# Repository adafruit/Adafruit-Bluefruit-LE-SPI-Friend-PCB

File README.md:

## Adafruit Bluefruit LE SPI Friend PCB

<a href="http://www.adafruit.com/products/2633"><br/>
Click here to purchase one from the Adafruit shop</a>

PCB files for the Adafruit Bluefruit LE SPI Friend PCB. Format is EagleCAD schematic and board layout
* https://www.adafruit.com/product/2633

### Description

The Bluefruit LE SPI Friend makes it easy to add Bluetooth Low Energy connectivity to anything with 4 or 5 GPIO pins. With SPI, you don't have to worry about baud rates, flow control, or giving up a hardware UART port. Connect to your Arduino or other microcontroller using the common four-pin SPI interface (MISO, MOSI, SCK and CS) plus a 5th GPIO pin for interrupts (to let the Arduino know when data or a response is ready).

This multi-function module can do quite a lot! For most people, they'll be very happy to use the standard Nordic UART RX/TX connection profile. In this profile, the Bluefruit acts as a data pipe, that can 'transparently' transmit back and forth from your iOS or Android device. You can use our iOS App or Android App, or write your own to communicate with the UART service.

### License

Adafruit invests time and resources providing this open source design, please support Adafruit and open-source hardware by purchasing products from [Adafruit](https://www.adafruit.com)!

Designed by Limor Fried/Ladyada for Adafruit Industries.

Creative Commons Attribution/Share-Alike, all text above must be included in any redistribution. See license.txt for additional details.

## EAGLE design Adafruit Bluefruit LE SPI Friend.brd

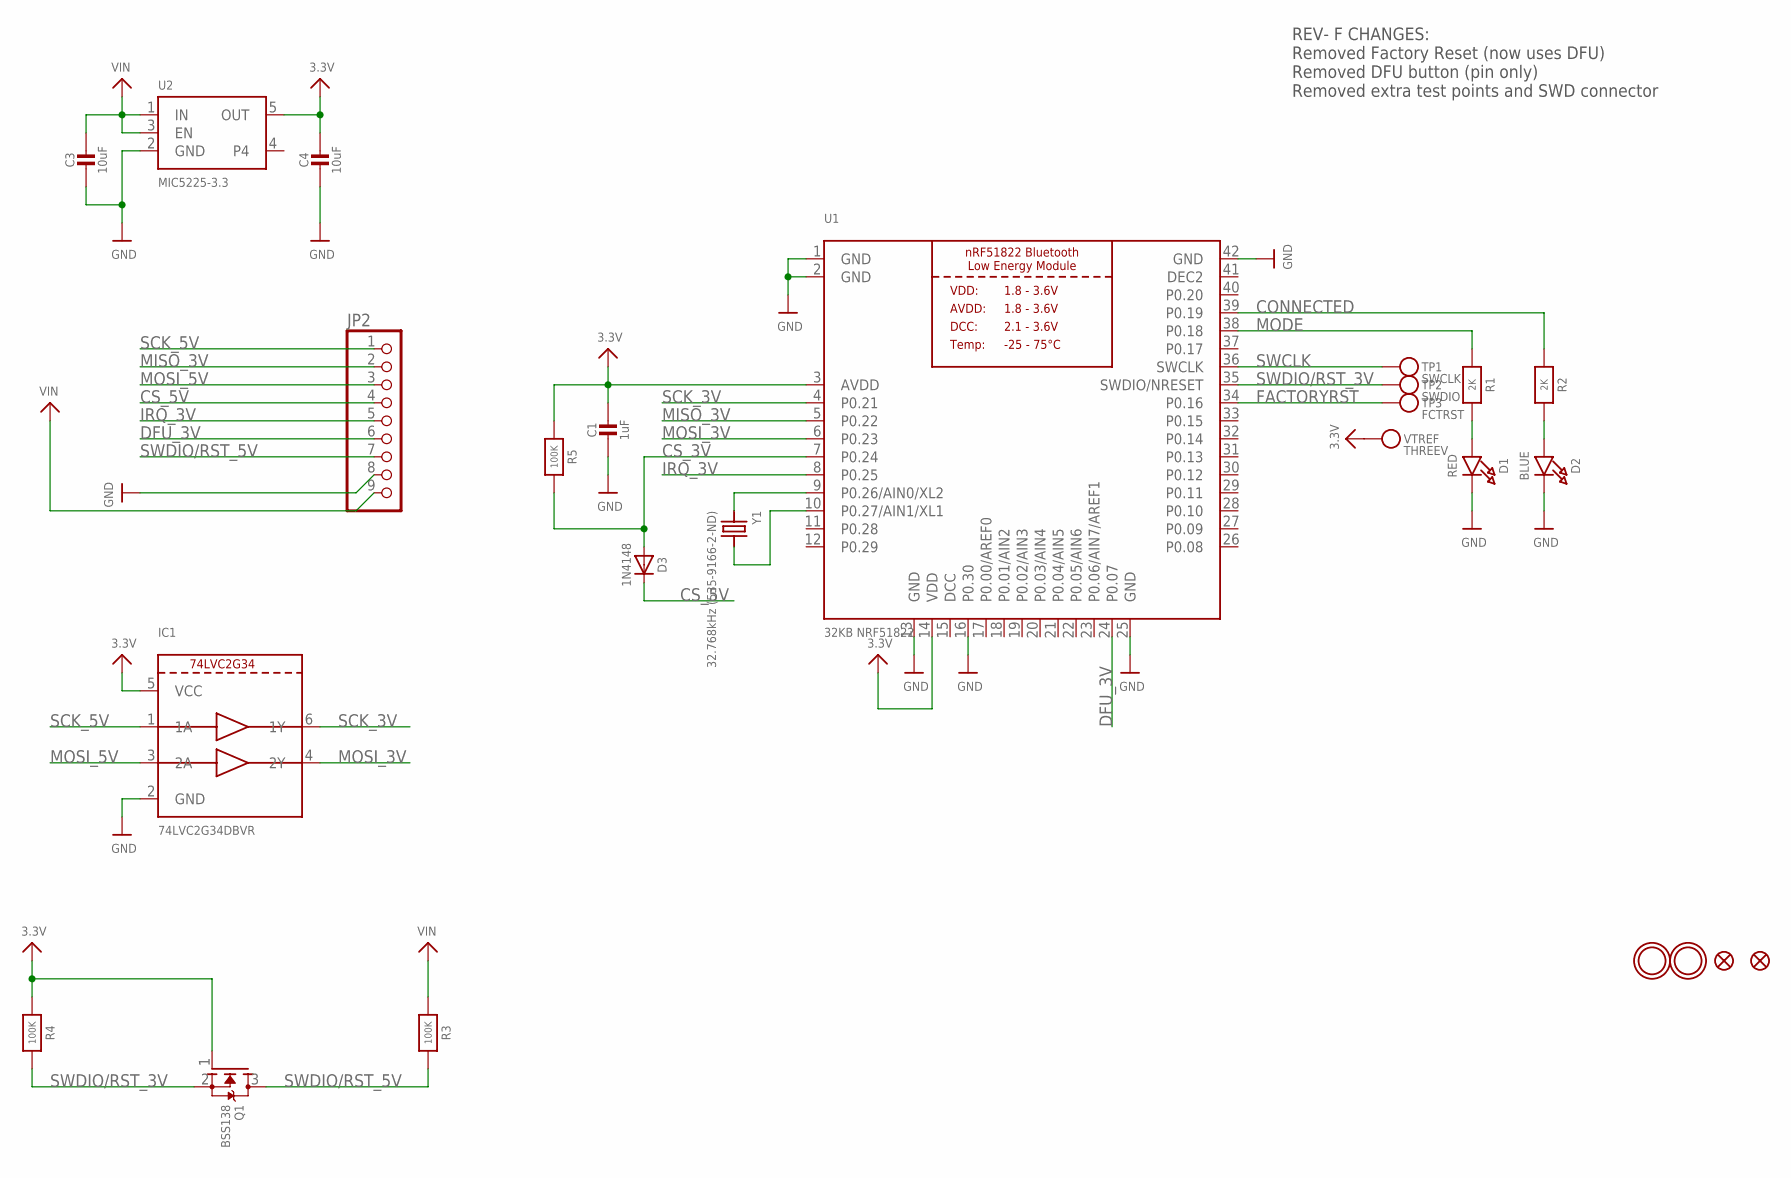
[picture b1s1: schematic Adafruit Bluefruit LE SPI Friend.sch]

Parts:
C1: 1uF; 0805_10MGAP
C3: 10uF; 0805-NO
C4: 10uF; 0805_10MGAP
D1: RED; CHIPLED_0805_NOOUTLINE
D2: BLUE; CHIPLED_0805_NOOUTLINE
D3: 1N4148; SOD-323
FID1, FID3: FIDUCIAL""; FIDUCIAL_1MM
IC1: 74LVC2G34DBVR; SOT23-6
JP2: HEADER-1X970MIL; 1X09_ROUND_70
Q1: BSS138; SOT23-WIDE@1
R1, R2: 2K; _0805MP
R3, R4: 100K; 0805-NO
R5: 100K; _0805MP
TP1: SWCLK; PAD-1.5X2.0
TP2: SWDIO; PAD-1.5X2.0
TP3: FCTRST; PAD-1.5X2.0
U1: 32KB NRF51822; BLE_MODULE_RAYTAC_MDBT40
U2: MIC5225-3.3; SOT23-5
U$28, U$29: MOUNTINGHOLE2.5; MOUNTINGHOLE_2.5_PLATED
VTREF: THREEV; PAD-1.5X2.0
Y1: 32.768kHz (535-9166-2-ND); CRYSTAL_CYL_2X6MM_SMT

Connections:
3.3V: C1.1, C4.1, IC1.5 (VCC), Q1.1 (G), R4.1, R5.1, U1.3 (AVDD), U1.14 (VDD), U2.5 (OUT), VTREF.P$1
CONNECTED: R2.1, U1.39 (P0.19)
CS_3V: D3.A, R5.2, U1.7 (P0.24)
CS_5V: D3.C, JP2.4
DCC: U1.15 (DCC)
DEC2: U1.41 (DEC2)
DFU_3V: JP2.6, U1.24 (P0.07)
FACTORYRST: TP3.P$1, U1.34 (P0.16)
GND: C1.2, C3.2, C4.2, D1.C, D2.C, IC1.2 (GND), JP2.8, U1.1 (GND), U1.2 (GND), U1.13 (GND), U1.16 (P0.30), U1.25 (GND), U1.42 (GND), U2.2 (GND)
IRQ_3V: JP2.5, U1.8 (P0.25)
MISO_3V: JP2.2, U1.5 (P0.22)
MODE: R1.1, U1.38 (P0.18)
MOSI_3V: IC1.4 (2Y), U1.6 (P0.23)
MOSI_5V: IC1.3 (2A), JP2.3
unnamed: U1.9 (P0.26/AIN0/XL2), Y1.1
unnamed: U1.10 (P0.27/AIN1/XL1), Y1.2
unnamed: D1.A, R1.2
unnamed: D2.A, R2.2
SCK_3V: IC1.6 (1Y), U1.4 (P0.21)
SCK_5V: IC1.1 (1A), JP2.1
SWCLK: TP1.P$1, U1.36 (SWCLK)
SWDIO/RST_3V: Q1.2 (S), R4.2, TP2.P$1, U1.35 (SWDIO/NRESET)
SWDIO/RST_5V: JP2.7, Q1.3 (D), R3.2
VIN: C3.1, JP2.9, R3.1, U2.1 (IN), U2.3 (EN)

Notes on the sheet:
REV- F CHANGES: Removed Factory Reset (now uses DFU) Removed DFU button (pin only) Removed extra test points and SWD connector

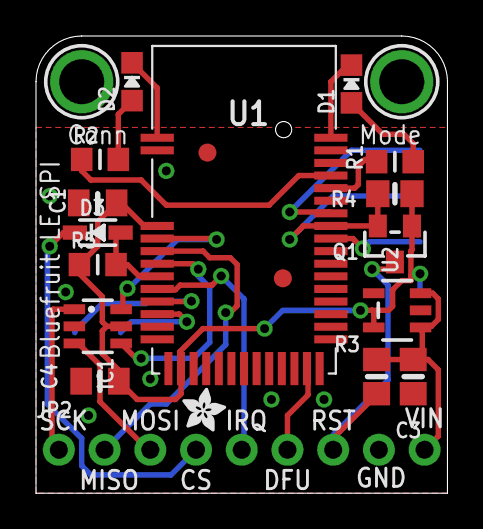
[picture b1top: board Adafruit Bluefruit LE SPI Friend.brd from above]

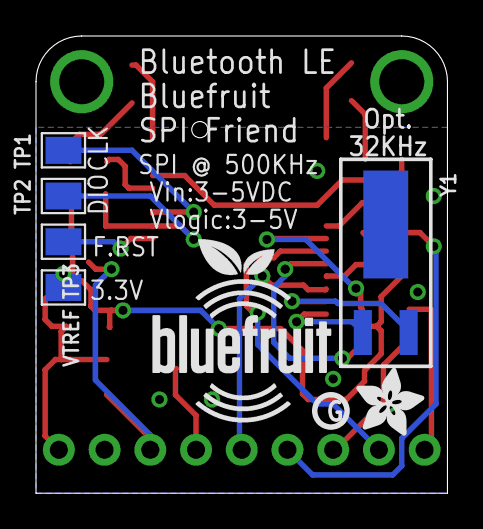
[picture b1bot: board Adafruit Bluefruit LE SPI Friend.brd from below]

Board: 2 copper layers, 22.9 x 25.4 mm, 29 parts (8 on the bottom side), 22 nets.

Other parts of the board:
U$3: ADAFRUIT_2.5MM
U$9: BLUEFRUITLOGO_100MM
U$17: ADAFRUIT_3.5MM
U$18: PCBFEAT-REV-040

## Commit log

2016-09-27 init

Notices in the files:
parts and their libraries:
microbuilder: This work is placed in the public domain, and may be freely used for commercial and non-commercial work with the following conditions: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
